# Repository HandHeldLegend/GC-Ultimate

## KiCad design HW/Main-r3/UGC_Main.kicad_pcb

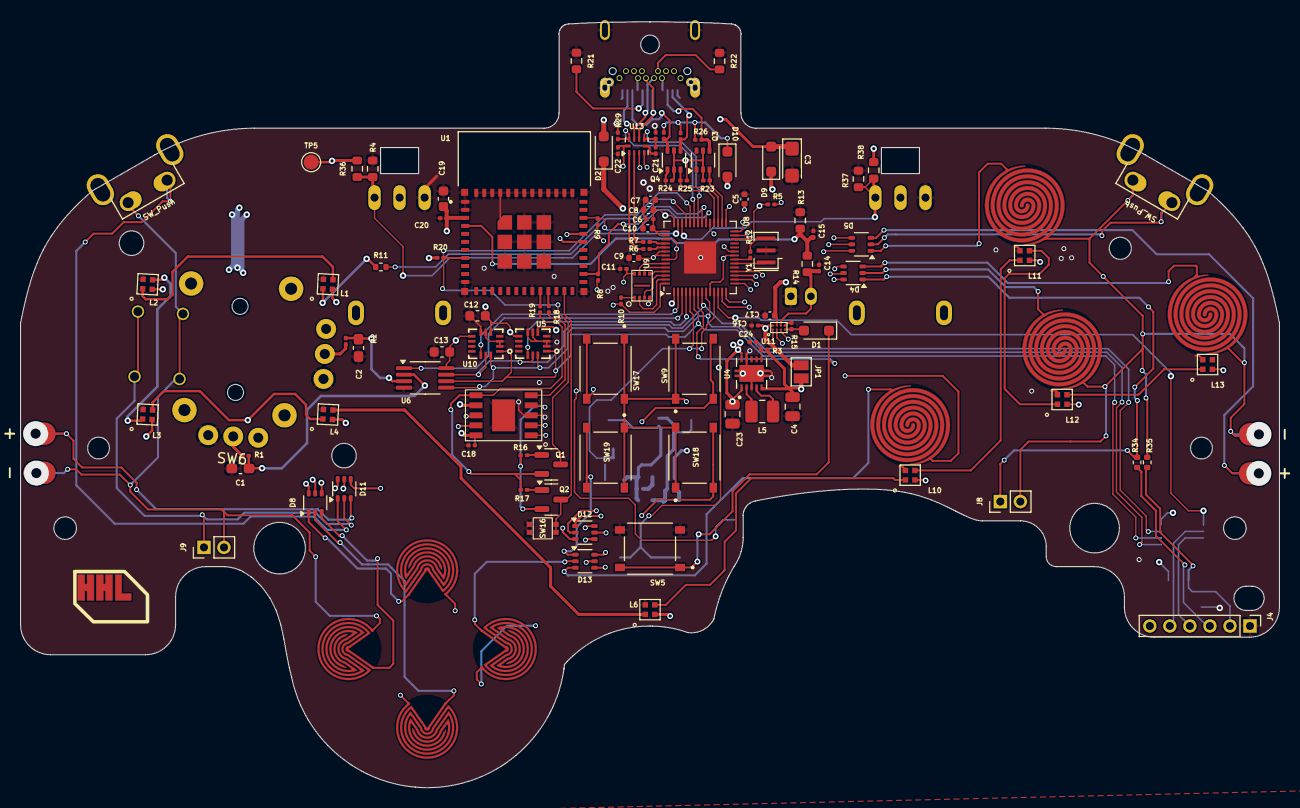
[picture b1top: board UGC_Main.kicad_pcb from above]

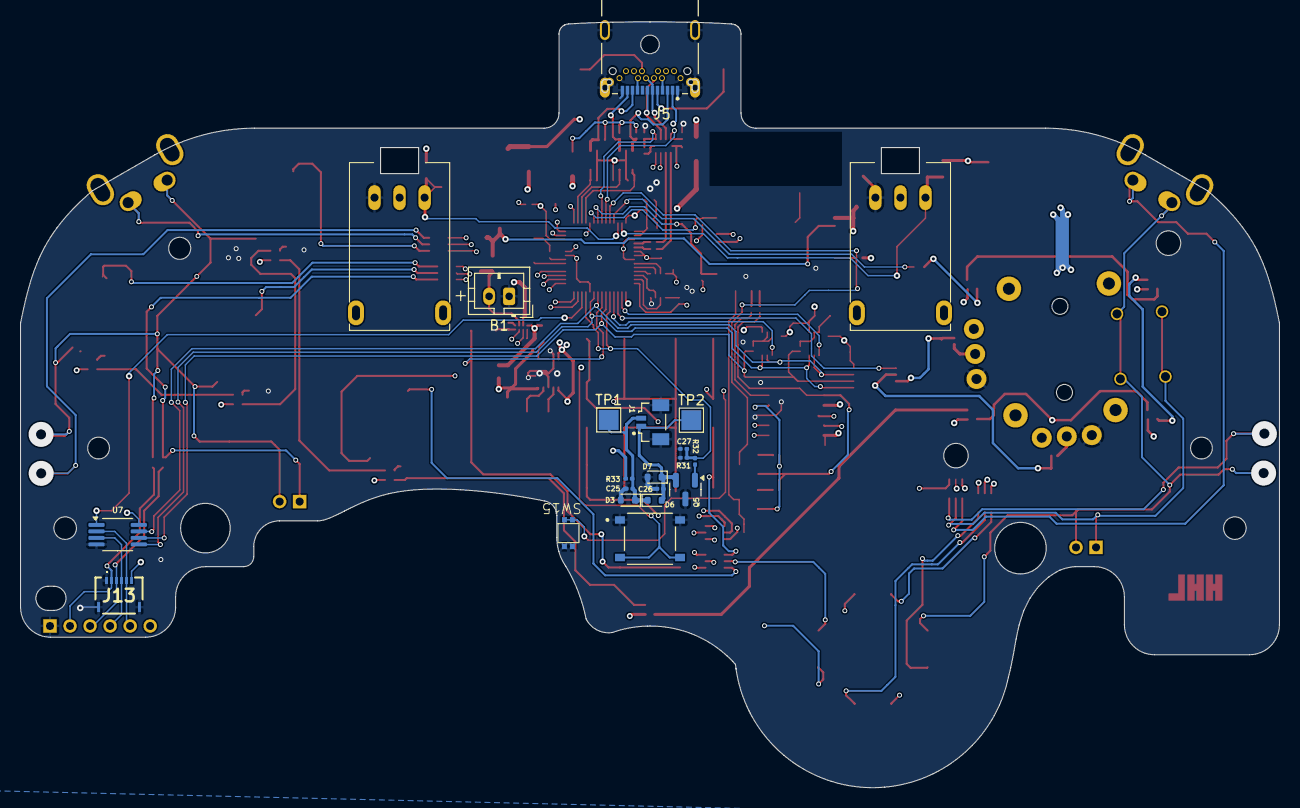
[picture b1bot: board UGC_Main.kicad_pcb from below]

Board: 4 copper layers, 125.7 x 76.4 mm, 139 parts (21 on the bottom side), 115 nets.

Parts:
B1: Battery; JST_PH_B2B-PH-K_1x02_P2.00mm_Vertical
C1, C2: .047u; C_0603_1608Metric_Pad1.08x0.95mm_HandSolder
C3: 47uF 6.3v; CP_EIA-3216-18_Kemet-A
C4, C23: 10uF; C_0805_2012Metric
C5, C7, C9, C10: 100n; C_0402_1005Metric
C6, C11, C15, C18, C20, C22, C24: 100n; C_0201_0603Metric
C8: 1u; C_0402_1005Metric
C12, C13: 100nF; C_0603_1608Metric
C14, C16, C21, C25, C26: 1u; C_0201_0603Metric
C17: 10uF; C_0402_1005Metric
C19: 10uF/10V (20%); C_0603_1608Metric
C27: 100nF; C_0201_0603Metric
D1, D2, D9, D10: CUS08F30; D_SOD-323_HandSoldering
D3, D6, D7: M7C; D_SOD-523
D4, D5, D8, D11, D12, D13: BAS16VY,115; SOT-363_SC-70-6
J1: SM02B-SURS-TF_LF__SN_; JST_SM02B-SURS-TF_LF__SN_
J2: LT; rumble_pins
J3: RT; rumble_pins
J4: Conn_01x06_Pin; PinHeader_1x06_P2.00mm_Vertical
J5: UJ31-CH-G1-SMT-TR; CUI_UJ31-CH-G1-SMT-TR
J8, J9: Conn_01x02; PinHeader_1x02_P2.00mm_Vertical
J13: 503480-0640; 5034800640
JP1: SolderJumper_2_Open; SolderJumper-2_P1.3mm_Open_Pad1.0x1.5mm
L1, L2, L3, L4, L6, L10, L11, L12, L13: SK6805-EC-15
L5: 1.3A 2.2uH ±20% 80mΩ; L_1008_2520Metric
Q1, Q2: MMBT3904; SOT-23
Q3, Q4: BSS138DW; SOT-363_SC-70-6
Q5: Q_NMOS_GSD; SOT-23
R1, R2, R8, R9, R10, R12, R23, R24, R25, R26, R27, R28: 1k; R_0201_0603Metric
R3: 100; R_0201_0603Metric
R4, R13, R14, R36, R37, R38: 75k; R_0603_1608Metric
R5, R15, R16, R17, R20, R29, R30, R31: 10k; R_0201_0603Metric
R6, R7: 27; R_0201_0603Metric
R11: 330; R_0402_1005Metric
R18, R19: 0; R_0201_0603Metric
R21, R22: 5.1kohm; R_0603_1608Metric
R32: 100R; R_0201_0603Metric
R33: 0R; R_0201_0603Metric
R34, R35: 0R; R_0402_1005Metric
RV1, RV2: Slider_GCC-Gamecube_MB; GCC_Slider
SW1, SW2, SW3, SW4: SW_Push; ring_pad
SW5, SW9, SW14, SW17, SW18, SW19: SW_TS-1187A; TS-1187A-C-E-B
SW6: GL18_SW; GL1807SYAE
SW7, SW8: SW_Push; Z_Switch_Edge_Omron
SW10, SW11, SW12, SW13: SW_Push; ring_dpad
SW15, SW16: 1TS026A-1000-0550
TP1, TP2: TestPoint; TestPoint_Pad_2.0x2.0mm
TP5: TestPoint; TestPoint_Pad_D1.5mm
U1: ESP32-PICO-MINI-02; MODULE_ESP32-PICO-MINI-02
U4: TPS630001RCR; VREG_V62_16624-01YE
U5, U10: ST_LSM6; LGA14
U6, U7: MCP3002; MSOP-8_3x3mm_P0.65mm
U8: RP2040; QFN-56-1EP_7x7mm_P0.4mm_EP3.2x3.2mm
U9: GD25Q80EEIGR; USON-8-EP(2x3)
U11: BQ25180; DSBGA
U12: CH340K; ESSOP-10
U13: PI3USB4000A; Texas_UQFN-10_1.5x2mm_P0.5mm
Y1: Crystal_GND3; Resonator_SMD_Murata_CSTxExxV-3Pin_3.0x1.1mm

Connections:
+1V1: C5.2, U8.23 (DVDD), U8.45 (VREG_VOUT), U8.50 (DVDD)
+3V3: C6.1, C7.1, C8.1, C9.2, C10.2, C11.1, C12.2, C13.2, C18.1, C19.1, C20.2, C22.1, C23.1, D10.2 (A), J4.6, J13.6, L1.2 (VDD), L2.2 (VDD), L3.2 (VDD), L4.2 (VDD), L6.2 (VDD), L10.2 (VDD), L11.2 (VDD), L12.2 (VDD), L13.2 (VDD), Q3.2 (G1), Q3.5 (G2), Q4.2 (G1), Q4.5 (G2), R5.1, R8.1, R9.2, R20.1, R23.1, R24.1, R25.1, R33.2, R36.2, R38.2, RV1.1 (GND), RV2.1 (GND), SW6.X3 (VCC), SW6.Y3 (VCC), TP5.1, U1.3 (3V3), U4.1 (VOUT), U4.10 (FB), U5.5 (VDDIO), U5.8 (VDD), U6.8 (VDD/VREF), U7.8 (VDD/VREF), U8.1 (IOVDD), U8.10 (IOVDD), U8.22 (IOVDD), U8.33 (IOVDD), U8.42 (IOVDD), U8.43 (ADC_AVDD), U8.44 (VREG_IN), U8.48 (USB_VDD), U8.49 (IOVDD), U9.8 (VCC), U10.5 (VDDIO), U10.8 (VDD), U12.7 (VCC), U12.10 (3V), U13.10 (VCC)
+3V3_PRE: C3.1, D9.2 (A), J5.A2 (SSTXP1), J5.B2 (SSTXP2)
+5V_PRE: D2.2 (A), J5.A4 (VBUS), J5.A9 (VBUS), J5.B4 (VBUS), J5.B9 (VBUS)
A: D4.6 (K), D8.6 (K), D12.6 (K), U8.29 (GPIO18)
ABXY_RGB: L6.3 (DOUT), L10.1 (DIN)
B: D4.5 (K), D8.5 (K), D12.5 (K), U8.28 (GPIO17)
BATTERY_POS: B1.2, C14.2, R14.2, U11.C2 (BAT)
BAT_LVL: C15.1, R13.2, R14.1, U1.4 (I36)
BTN_PWR: D1.1 (K), SW5.A, SW5.B, U8.7 (GPIO5)
C: D4.4 (K), D8.4 (K), D12.4 (K), U8.27 (GPIO16)
CC1: J5.A5 (CC1), R21.2
CC2: J5.B5 (CC2), R22.2
D: D5.6 (K), D11.6 (K), D13.6 (K), U8.18 (GPIO15)
D+: J5.A6 (DP1), J5.B6 (DP2), U13.8 (C+)
D-: J5.A7 (DN1), J5.B7 (DN2), U13.7 (C-)
E: D5.5 (K), D11.5 (K), D13.5 (K), U8.17 (GPIO14)
ESP_CTS: R18.2, U12.5 (CTS)
ESP_DTR: Q2.2 (E), R16.1, U12.4 (DTR)
ESP_EN: Q1.3 (C), R20.2, U1.8 (EN), U8.38 (GPIO26_ADC0)
ESP_IO0: Q2.3 (C), SW16.3, SW16.4, U1.23 (IO0)
ESP_IO13: R19.2, U1.20 (IO13)
ESP_IO15: R18.1, U1.21 (IO15)
ESP_RTS: Q1.2 (E), R17.2, R19.1, U12.6 (RTS)
ESP_RX0: U1.30 (RXD0), U12.8 (TXD)
ESP_TX0: U1.31 (TXD0), U12.9 (RXD)
F: D5.4 (K), D11.4 (K), D13.4 (K), U8.16 (GPIO13)
G: J3.2, J8.2, R35.2, SW1.1, SW3.1, SW4.1, SW8.1, U8.15 (GPIO12)
GND: B1.1, C1.1, C2.1, C3.2, C4.1, C5.1, C6.2, C7.2, C8.2, C9.1, C10.1, C11.2, C12.1, C13.1, C14.1, C15.2, C16.2, C17.1, C18.2, C19.2, C20.1, C21.2, C22.2, C23.2, C24.1, C25.1, C26.2, C27.2, D3.2 (A), D7.2 (A), J1.S1 (SHIELD), J1.S2 (SHIELD), J4.1, J5.A1 (GND), J5.A12 (GND), J5.B1 (GND), J5.B12 (GND), J5.SH1 (SHIELD), J5.SH2 (SHIELD), J5.SH3 (SHIELD), J5.SH4 (SHIELD), J5.SH5 (SHIELD), J5.SH6 (SHIELD), J13.1, J13.MP1, J13.MP2, L1.4 (GND), L2.4 (GND), L3.4 (GND), L4.4 (GND), L6.4 (GND), L10.4 (GND), L11.4 (GND), L12.4 (GND), L13.4 (GND), Q5.3 (D), R4.1, R13.1, R15.2, R21.1, R22.1, R29.1, R30.2, R31.1, R37.1, RV1.3 (V+), RV2.3 (V+), SW5.C, SW5.D, SW6.X1 (GND), SW6.Y1 (GND), SW14.A, SW14.B, SW15.1, SW15.2, SW16.1, SW16.2, U1.1 (GND), U1.2 (GND), U1.11 (GND), U1.14 (GND), U1.19 (IO12), U1.36 (GND), U1.37 (GND), U1.38 (GND), U1.39 (GND), U1.40 (GND), U1.41 (GND), U1.42 (GND), U1.43 (GND), U1.44 (GND), U1.45 (GND), U1.46 (GND), U1.47 (GND), U1.48 (GND), U1.49 (GND), U1.50 (GND), U1.51 (GND), U1.52 (GND), U1.53 (GND), U1.54 (GND), U1.55 (GND), U1.56 (GND), U1.57 (GND), U1.58 (GND), U1.59 (GND), U1.60 (GND), U1.61 (GND), U4.3 (PGND), U4.9 (GND), U4.11 (EP), U5.2 (SDx), U5.3 (SCx), U5.6 (GNDIO), U5.7 (GND), U6.4 (VSS), U7.4 (VSS), U8.19 (TESTEN), U8.57 (GND), U9.4 (VSS), U10.2 (SDx), U10.3 (SCx), U10.6 (GNDIO), U10.7 (GND), U11.D2 (GND), U12.3 (GND), U12.11 (GND), U13.5 (GND), Y1.2
H: J2.2, J9.2, SW6.S1 (1), SW6.S2 (2), SW7.1, SW10.1, SW11.1, SW12.1, U8.14 (GPIO11)
I: SW2.1, SW9.A, SW9.B, SW13.1, SW17.A, SW17.B, SW18.A, SW18.B, SW19.A, SW19.B, U8.13 (GPIO10)
I2C_SCL: R8.2, U1.26 (IO20), U8.35 (GPIO23), U11.B1 (SCL)
I2C_SDA: R9.1, U1.33 (IO19), U8.34 (GPIO22), U11.C1 (SDA)
IMU0_CS: U8.2 (GPIO0), U10.12 (CS)
IMU1_CS: U5.12 (CS), U8.4 (GPIO2)
LADC_CS: U6.1 (~CS/SHDN), U8.3 (GPIO1)
LRA+: C25.2, D3.1 (K), D6.1 (K), J1.2, R33.1, TP1.1
LRA-: C26.1, D6.2 (A), D7.1 (K), J1.1, Q5.2 (S), TP2.1
LRA_HI: C27.1, R31.2, R32.1, U8.5 (GPIO3), U8.11 (GPIO8)
LS_BTN_IN: D11.2 (A), J9.1, SW6.S3 (3), SW6.S4 (4)
LX: C1.2, R1.2, U6.2 (CH0)
LY: C2.2, R2.2, U6.3 (CH1)
N_CLOCK: J5.A3 (SSTXN1), J5.B3 (SSTXN2), Q4.6 (D1), R27.2
N_CLOCK_3.3: Q4.1 (S1), R24.2, U8.32 (GPIO21)
N_DATA: J5.A11 (SSRXP2), J5.B11 (SSRXP1), Q4.4 (S2), R28.2
N_DATA_3.3: Q4.3 (D2), R25.2, U8.31 (GPIO20)
N_LATCH: J5.A10 (SSRXN2), J5.B10 (SSRXN1), Q3.4 (S2), R26.2
N_LATCH_3.3: Q3.3 (D2), R23.2, U8.30 (GPIO19)
unnamed: D1.2 (A), R15.1, U11.D1 (TS/MR)
unnamed: D4.1 (A), J8.1, R34.1
unnamed: D4.2 (A), SW1.2
unnamed: D4.3 (A), SW3.2
unnamed: D5.1 (A), SW4.2
unnamed: D5.2 (A), SW8.2
unnamed: D5.3 (A), J3.1
unnamed: D8.1 (A), SW10.2
unnamed: D8.2 (A), SW11.2
unnamed: D8.3 (A), SW12.2
unnamed: D11.1 (A), SW7.2
unnamed: D11.3 (A), J2.1
unnamed: D12.1 (A), SW9.C, SW9.D
unnamed: D12.2 (A), SW17.C, SW17.D
unnamed: D12.3 (A), SW18.C, SW18.D
unnamed: D13.1 (A), SW19.C, SW19.D
unnamed: D13.2 (A), SW13.2
unnamed: D13.3 (A), SW2.2
unnamed: L1.3 (DOUT), L2.1 (DIN)
unnamed: L2.3 (DOUT), L3.1 (DIN)
unnamed: L3.3 (DOUT), L4.1 (DIN)
unnamed: L10.3 (DOUT), L11.1 (DIN)
unnamed: L11.3 (DOUT), L12.1 (DIN)
unnamed: L12.3 (DOUT), L13.1 (DIN)
unnamed: Q1.1 (B), R16.2
unnamed: Q2.1 (B), R17.1
unnamed: Q5.1 (G), R32.2
unnamed: R12.1, Y1.3
unnamed: R1.1, SW6.X2 (X_OUT)
unnamed: R2.1, SW6.Y2 (Y_OUT)
unnamed: C24.2, R3.2, U4.6 (EN), U4.7 (PS/SYNC), U4.8 (VINA)
unnamed: L5.1, U4.4 (L1)
unnamed: L5.2, U4.2 (L2)
unnamed: R7.2, U8.46 (USB_DM)
unnamed: R6.2, U8.47 (USB_DP)
unnamed: R10.2, U9.1 (/CS)
PLAYER_RGB: L4.3 (DOUT), L6.1 (DIN)
RADC_CS: U7.1 (~CS/SHDN), U8.12 (GPIO9)
RGB_OUT: R11.2, U8.39 (GPIO27_ADC1)
RP_RUN: R5.2, SW14.C, SW14.D, U8.26 (RUN)
RP_USB+: R6.1, U13.1 (L0+)
RP_USB-: R7.1, U13.2 (L0-)
RS_B_IN: J4.2, J13.2, R35.1
RS_B_OUT: J4.3, J13.3, R34.2
RX: J4.5, J13.5, U7.2 (CH0)
RY: J4.4, J13.4, U7.3 (CH1)
SCLK: U8.52 (QSPI_SCLK), U9.6 (SCLK)
SHARED_PU: D10.1 (K), R26.1, R27.1, R28.1
SIO0: U8.53 (QSPI_SD0), U9.5 (IO0)
SIO1: U8.55 (QSPI_SD1), U9.2 (IO1)
SIO2: U8.54 (QSPI_SD2), U9.3 (IO2)
SIO3: U8.51 (QSPI_SD3), U9.7 (IO3)
SL_RGB: L1.1 (DIN), R11.1
SPI_CK: U5.13 (SCL), U6.7 (CLK), U7.7 (CLK), U8.8 (GPIO6), U10.13 (SCL)
SPI_RX: U5.1 (SDO), U6.6 (DOUT), U7.6 (DOUT), U8.6 (GPIO4), U10.1 (SDO)
SPI_TX: U5.14 (SDA), U6.5 (DIN), U7.5 (DIN), U8.9 (GPIO7), U10.14 (SDA)
UART_USB+: U12.1 (D+), U13.3 (L1+)
UART_USB-: U12.2 (D-), U13.4 (L1-)
USB_BOOT: R10.1, SW15.3, SW15.4, U8.56 (QSPI_SS)
USB_EN: C21.1, R30.1, U8.36 (GPIO24), U13.6 (/EN)
USB_SEL: R29.2, U8.37 (GPIO25), U13.9 (SEL)
VBUS: C16.1, D2.1 (K), JP1.1 (A), U11.A2 (IN)
VBUS_SYS: C4.2, C17.2, D9.1 (K), JP1.2 (B), R3.1, U4.5 (VIN), U11.B2 (SYS)
XTAL_IN: U8.20 (XIN), Y1.1
XTAL_OUT: R12.2, U8.21 (XOUT)
ZL_ANALOG: R4.2, R36.1, RV1.2 (Signal), U8.41 (GPIO29_ADC3)
ZR_ANALOG: R37.2, R38.1, RV2.2 (Signal), U8.40 (GPIO28_ADC2)

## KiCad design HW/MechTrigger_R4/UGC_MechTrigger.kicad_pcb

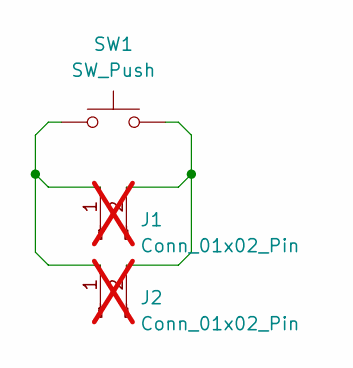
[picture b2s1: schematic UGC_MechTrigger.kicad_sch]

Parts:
J1, J2: Conn_01x02_Pin; PinHeader_1x02_P2.54mm_Vertical; not fitted
SW1: SW_Push; PG1353; MPN CPG135301D03

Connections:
unnamed: J1.1, J2.1, SW1.1
unnamed: J1.2, J2.2, SW1.2

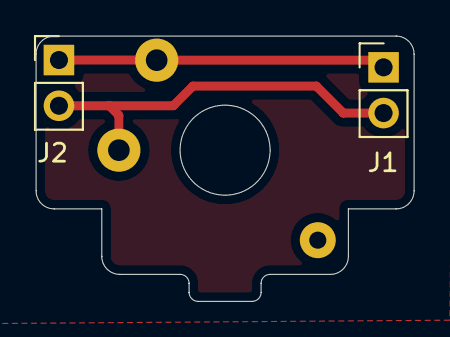
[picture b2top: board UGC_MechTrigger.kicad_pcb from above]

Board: 2 copper layers, 21.0 x 14.7 mm, 3 parts (0 on the bottom side), 2 nets.

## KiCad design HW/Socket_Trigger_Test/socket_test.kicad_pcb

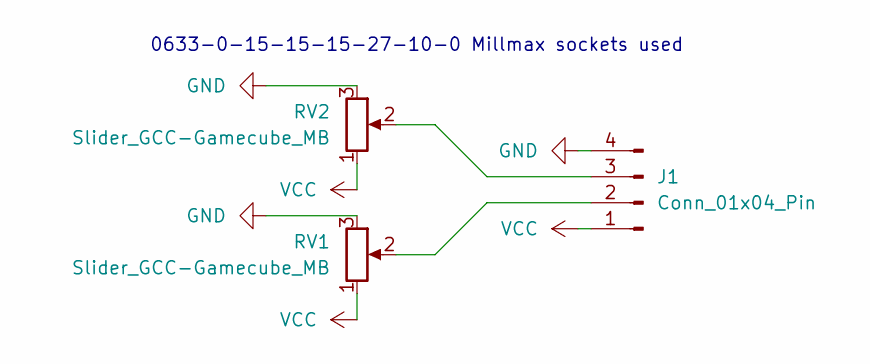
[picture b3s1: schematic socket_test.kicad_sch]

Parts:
J1: Conn_01x04_Pin; JST_EH_B4B-EH-A_1x04_P2.50mm_Vertical
RV1, RV2: Slider_GCC-Gamecube_MB; GCC_Slider_MillMax

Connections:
GND: J1.4, RV1.3 (V+), RV2.3 (V+)
unnamed: J1.2, RV1.2 (Signal)
unnamed: J1.3, RV2.2 (Signal)
VCC: J1.1, RV1.1 (GND), RV2.1 (GND)

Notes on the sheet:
0633-0-15-15-15-27-10-0 Millmax sockets used

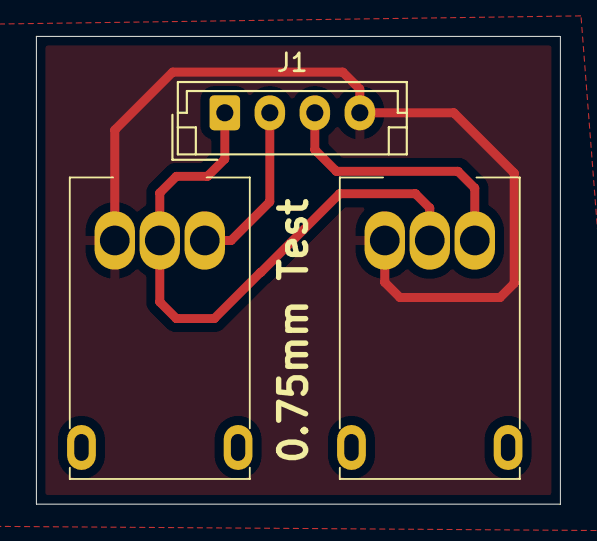
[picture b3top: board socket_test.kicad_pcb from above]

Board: 2 copper layers, 29.1 x 26.0 mm, 3 parts (0 on the bottom side), 4 nets.

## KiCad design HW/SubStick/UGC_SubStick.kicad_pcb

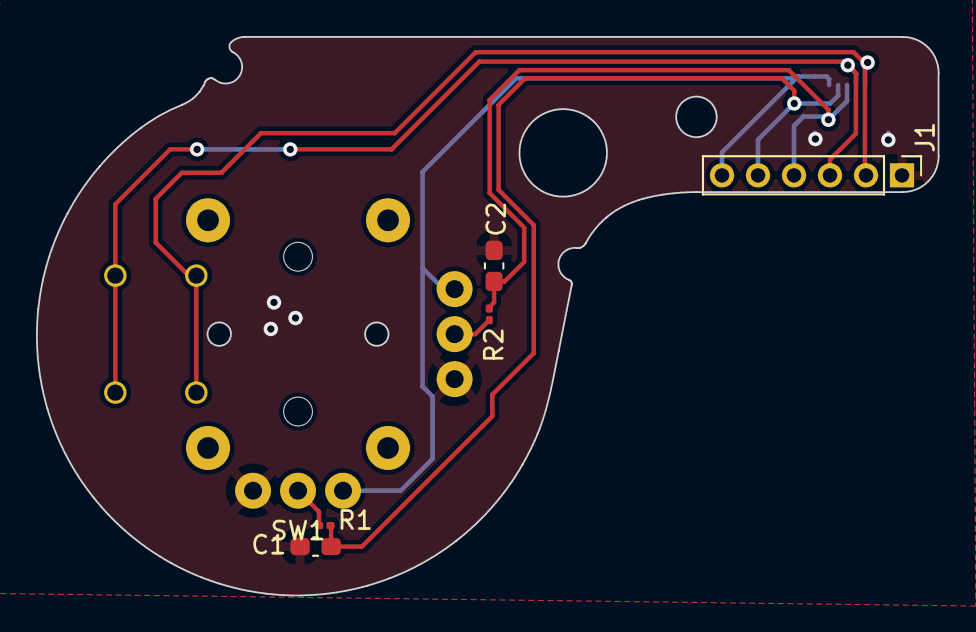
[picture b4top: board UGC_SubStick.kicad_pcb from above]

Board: 2 copper layers, 50.1 x 31.0 mm, 7 parts (1 on the bottom side), 8 nets.

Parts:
C1, C2: .047u; C_0603_1608Metric_Pad1.08x0.95mm_HandSolder
J1: Conn_01x06_Pin; PinHeader_1x06_P2.00mm_Vertical
J2: 503480-0640; 5034800640
R1, R2: 1k; R_0201_0603Metric
SW1: GL18_SW; GL1807SYAE

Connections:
+3V3: J1.6, J2.6, SW1.X3 (VCC), SW1.Y3 (VCC)
GND: C1.1, C2.1, J1.1, J2.1, J2.MP1, J2.MP2, SW1.X1 (GND), SW1.Y1 (GND)
unnamed: R1.1, SW1.X2 (X_OUT)
unnamed: R2.1, SW1.Y2 (Y_OUT)
RS_B_IN: J1.3, J2.3, SW1.S3 (3), SW1.S4 (4)
RS_B_OUT: J1.2, J2.2, SW1.S1 (1), SW1.S2 (2)
RX: C1.2, J1.5, J2.5, R1.2
RY: C2.2, J1.4, J2.4, R2.2
